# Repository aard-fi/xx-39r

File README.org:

* XX-39R                                                              :TOC_4:
- [[#overview][Overview]]
- [[#licensing][Licensing]]
- [[#quick-springtide-40-conversion-guide][Quick springtide 40 conversion guide]]
- [[#xx-39r265c27-3-the-original-hardware][XX-39R/265C27-3, the original hardware]]
- [[#elrs-replacement][ELRS replacement]]
  - [[#firmware][Firmware]]
    - [[#variants][Variants]]
    - [[#building][Building]]
    - [[#flashing][Flashing]]
    - [[#fuses][Fuses]]
  - [[#verify-functionality][Verify functionality]]

* Overview

This repository is for documenting a pretty bad receiver and motor driver board for a RC boat labeled =XX-39R= and =265C27-3=, as well as a replacement for it. The board can be found in models like "Revell Spring Tide 40", but has no place in a toy from this decade (or the last) - the reception is absolutely horrible, and there are better options available nowadays.

Read the sections below for a more detailed board description, as well as our "absolute overkill" option for replacing it with something better. While the replacement board is designed as drop in replacement for this model it has been designed with reusability for other small models in mind as well - which also would be listed here.

* Licensing

All source code is licensed under [[https://www.google.com/url?sa=t&source=web&rct=j&opi=89978449&url=https://www.gnu.org/licenses/old-licenses/gpl-2.0.en.html&ved=2ahUKEwir6f6Xoo6VAxVaGBAIHQJ2DeoQFnoECBIQAQ&usg=AOvVaw0XM7ZibsgscQZj5xHzFtb8][GPLv2]]. PCB related KiCad files are licensed under [[https://creativecommons.org/licenses/by-nc-sa/4.0/][CC BY-NC-SA 4.0]].

* Quick springtide 40 conversion guide

Open all the screws on the boat, and open the small electronics box. Submerge the board into isopropyl alcohol for roughly 24 hours - and while wet, remove the plugs. They should come out relatively easy now.
Remove the antenna wire from the hole, and remove the board.

Assuming you have a board populated with SMD components, now you'll need to

- solder JST-PH 2.0 headers into J1, J2, J3 and J4
- solder a jumper into or bridge J13
- solder a pin header (male or female - female might be more comfortabe with some programmers) into J5
- solder a pin header into J6. Recommendation would be angled male, and female on the ELRS receiver

The layout is the same as the original - the JST headers and the ELRS module most go to the underside of the board (inside the silk screen markings). For the programmer an angled header has space on top as well, and can allow for easier reflashing.

Next you can connect your UPDI programmer to the board and the PC, download the latest firmware archive from the release page, unzip, and run =flash.sh= (Linux/MacOS) or =flash.ps1= (Windows), and follow the instructions. Select the 10MHz springtide firmware, and decide if you want the water sensor.

Plug in the ELRS receiver and he motor, battery and sensor wires. Do a quick functionality test with batteries and a remote and then put everything together.

* XX-39R/265C27-3, the original hardware

The board is built around the [[https://www.talkingelectronics.com/projects/27MHz%20Transmitters/imagesP2/RX2Bdatasheet-5function.pdf][TX-2B/RX-2B]] transmitter/receiver combo. The problem here is less with that chip, but more that it can be used with the cheapest possible receiver circuit (in this case, tuned to 40MHz), which does not behave well in the real world.

The remote control has 4 buttons: binary inputs for reverse/forward for each of the motors. So no speed control, and steering by only using one motor (or reversing the other, for tight turns).

The motor controller is a [[https://www.lcsc.com/product-detail/Motor-Driver-ICs_Mixic-MX1616H_C5119044.html][MX1616H]] - which is a reasonable choice for a boat powered by 4.5V.

Additionally, there's a protection circuit to detect a current between the two motors to avoid activation outside of the water.

The schematic in the =pcb= directory currently should be mostly complete, with the exception of the receiver circuit.

* ELRS replacement

For our replacement we're relying on an ELRS receiver. While absolute overkill for such a boat it'll allow a nice upgrade path to larger models later on. The hardware can support any small receivers using a serial protocol - so if you have spare older receivers around it can be adapted to use that instead. We don't want to touch other parts of the boat - so while we could use 14500 cells instead of AA we'd have to lower the voltage to make sure we don't burn out the motors.

The easier way is to just stick with the 4.5V architecture, and only boost voltage for the ELRS receiver.

We can reuse the motor controller as well as the protection circuit - but as we want to support the cheapest possible ELRS remotes we can't rely on track mixing in the remote, and therefore need a cheap microcontroller to interface between the receiver and the motor controller. We can use an AtTiny414 for that - it'll work over the complete voltage range we can expect this to operate at. An AtTiny412 would be possible - but we'd have to reuse the UPDI pin.

All unused pins on the MCU are lead out, as well as some spare footprints for VCC and GND pins. The complete table of pin headers is:

| Reference | Description     | Comment                                                                |
|-----------+-----------------+------------------------------------------------------------------------|
| J1        | Sense           |                                                                        |
| J2        | Battery         | Designed for 4.5V, but can take up to 5.5V                             |
| J3        | Port motor      |                                                                        |
| J4        | Starboard motor |                                                                        |
| J5        | UPDI            |                                                                        |
| J6        | Receiver        | Designed for ELRS, but can be used otherwise as well. See pinout below |
| J7        | PA6             |                                                                        |
| J8        | PA1             |                                                                        |
| J9        | PA3             |                                                                        |
| J10       | PA2             |                                                                        |
| J11       | Spare VCC       |                                                                        |
| J12       | Spare VCC       |                                                                        |
| J13       | Receiver VCC    | Bridge to use the on board booster, or connect your own                |
| J14       | Spare GND       |                                                                        |
| J15       | Spare GND       |                                                                        |
| J16       | Spare GND       |                                                                        |

The header for the (ELRS) receiver (=J6=) has the following pinout:

| Pin | ELRS | MCU           | Pin |
|-----+------+---------------+-----|
|   1 | GND  | GND           |     |
|   2 | VCC  | -             |     |
|   3 | TX   | PB3, UART1 RX |   6 |
|   4 | RX   | PB2, UART1 TX |   7 |

Any receiver using a serial protocol (like FlySky AFHDS) could be used, though the firmware here only supports ELRS.

The motor headers are connected as follows:

|           |          |       |      |     |          |
|-----------+----------+-------+------+-----+----------|
| Port      | J3 pin 1 | OUTA1 | INA1 | PA4 | =M1_FWD=   |
|           | J3 pin 2 | OUTB1 | INB1 | PA5 | =M1_REV=   |
| Starboard | J4 pin 1 | OUTA2 | INA2 | PB0 | =M2_FWD=   |
|           | J4 pin 2 | OUTB2 | INB2 | PB1 | =M2_REV= |

** Firmware

This is build with =common.hpp= containing code for all bigger features, and the individual firmware variants can use that to build model specific variants in less than 50 lines of code.

Common features are

- direction-change dead time (~50–80 ms coast) prevents regenerative voltage spikes
- rate limiting (±25 PWM per packet accel) makes it both more controllable (kid friendly) and prevents hardware destroying voltage spikes
- low-voltage cutoff (2.8 V) can stop motors before brownout
- custom CRSF parser, somewhat resilient: we try to re-sync if we read too much garbage, and stop the motors if we can't get it back
- water sensor readings, in safety mode (motors directly shut off) or just reading for extra data
- battery voltage readings
- support for different CPU speeds: 5, 10, 16 and 20MHz
- simple RX and TX buffering for UART communications
- optional "kickstart" support: on slow speeds do occasional kicks to get the motor started

*** Variants

We can build variants with extra features from base sources, with the filename containing markers to show what it is:

- *-ks* — Motor kickstart enabled (helps low-speed startup)
- *-ws* — Water safety sensor enabled. Recommended for kids - motors stop when the boat is removed from the water.
- *-5m*, *-10m*, *-16m* — CPU frequency variants (default = 20 MHz)

All release builds have frequency markers, only manual builds for development targets come without that, in which case 20MHz is assumed.

When running a model from batteries you generally should be using the 10MHz variant - that should be stable until relatively low voltages still. See fuse settings below if you want to push it even further by utilising brownout detection.

*** Building

Building only requires [[https://gcc.gnu.org/wiki/avr-gcc][avr-gcc]], and avr-libc in a variant new enough to have headers compatible with AtTiny414. On any sensible Linux distribution just installing those via the package manager should be fine, if you're using Ubuntu you can get a recent enough binary tarball via [[https://github.com/modm-io/avr-gcc][modm-io]].

On MacOS via homebrew you could do =brew tap osx-cross/avr && brew install avr-gcc@15=. Make sure it's in your path - either add it, or force linking it.

=make all-freqs= builds all variants.  Individual targets work too:

=make build/firmware-test-10m.hex= builds a single suffixed hex for 10 MHz.

=make FREQ=10m MOTOR_STALL_SPEED=120 all= customises stall speed before building.

*** Flashing

Flashing requires avrdude, as well as some UPDI programmer. Something like the [[https://www.adafruit.com/product/5879][UPDI friend]] is recommended, though you can [[https://github.com/ElTangas/jtag2updi][use some old Arduino]] as well.

When building from source =make flash= can be used - it will try to write =firmware.hex= to a UPDI programmer at =/dev/ttyUSB1=. You can override the firmware to flash with the =TARGET= variable, and the serial port with =PORT=: =make flash TARGET=firmware-test-pwm-starboard TARGET=/dev/ttyUSB0= would write the starboard motor test firmware via =ttyUSB0=.

Directly with avrdude the command for that would be =avrdude -c serialupdi -p t414 -U flash:w:firmware-test-pwm-starboard.hex:i -P /dev/ttyUSB0=

If you downloaded a release with prebuilt hex files, use the interactive scripts in =scripts/=:

- macOS / Linux: =./scripts/flash.sh=
- Windows: =powershell -ExecutionPolicy Bypass -File .\scripts\flash.ps1=

These scripts auto-detect your programmer, show current fuse values in plain English, and guide you through firmware selection.

*** Fuses

There are two fuses interesting for us:

- *BODCFG = 0x0A* — Brown-out detection enabled at 2.6 V
- *OSCCFG = 0x02* — 20 MHz internal oscillator

OSCCFG only needs to be set when running at 16MHz.

BODCFG configures the brownout detector, which can be useful to ensure the system gets back into a defined state when playing close to voltage limits.

Set with avrdude, or the included flash scripts.

** Verify functionality

This repository contains various specialised firmware bits to help debugging.

If the serial port is not working:

- flash =firmware-test-pb2= and check for a square wave on the =TX= pin of the ELRS header, and move on to =PB2= (pin 7) if there is none. This will either verify that the pin can be used - or point towards a hardware issue
- if the square wave test worked flash =firmware-test-uart= - this should be visible on the oscilloscope with the same settings, and a connected serial adapter should start printing =U=

For testing the motors:

- flash =firmware-test-gpio=. This will print to the serial port what it is testing, and will bitbang each motor port. Connected motors should spin up (in both directions), and this should be visible on a multimeter or oscilloscope
- flash =firmware-test-port= or =firmware-test-starboard= - those will cycle the port/starboard motor through reverse and forward PWM. If both spin correctly in both directions the motors are fine

For testing the water sensing:

- flash =firmware-test-water= and bridge J1, either with finger/metal or by sticking cables into water. It'll dump readings via serial

With all of the above sorted out you can flash =firmware-test= for a simple interactive serial interface to control all of the above. It'll spam a banner to serial until it receives a first keypress.

Steering should be channel 1 idle 0, -100 to 100. throttle should be channel 3, idle -100, up to 100.

Channels 5 and 8 may be used as toggle switches, channels 6 and 7 as tristate switches.

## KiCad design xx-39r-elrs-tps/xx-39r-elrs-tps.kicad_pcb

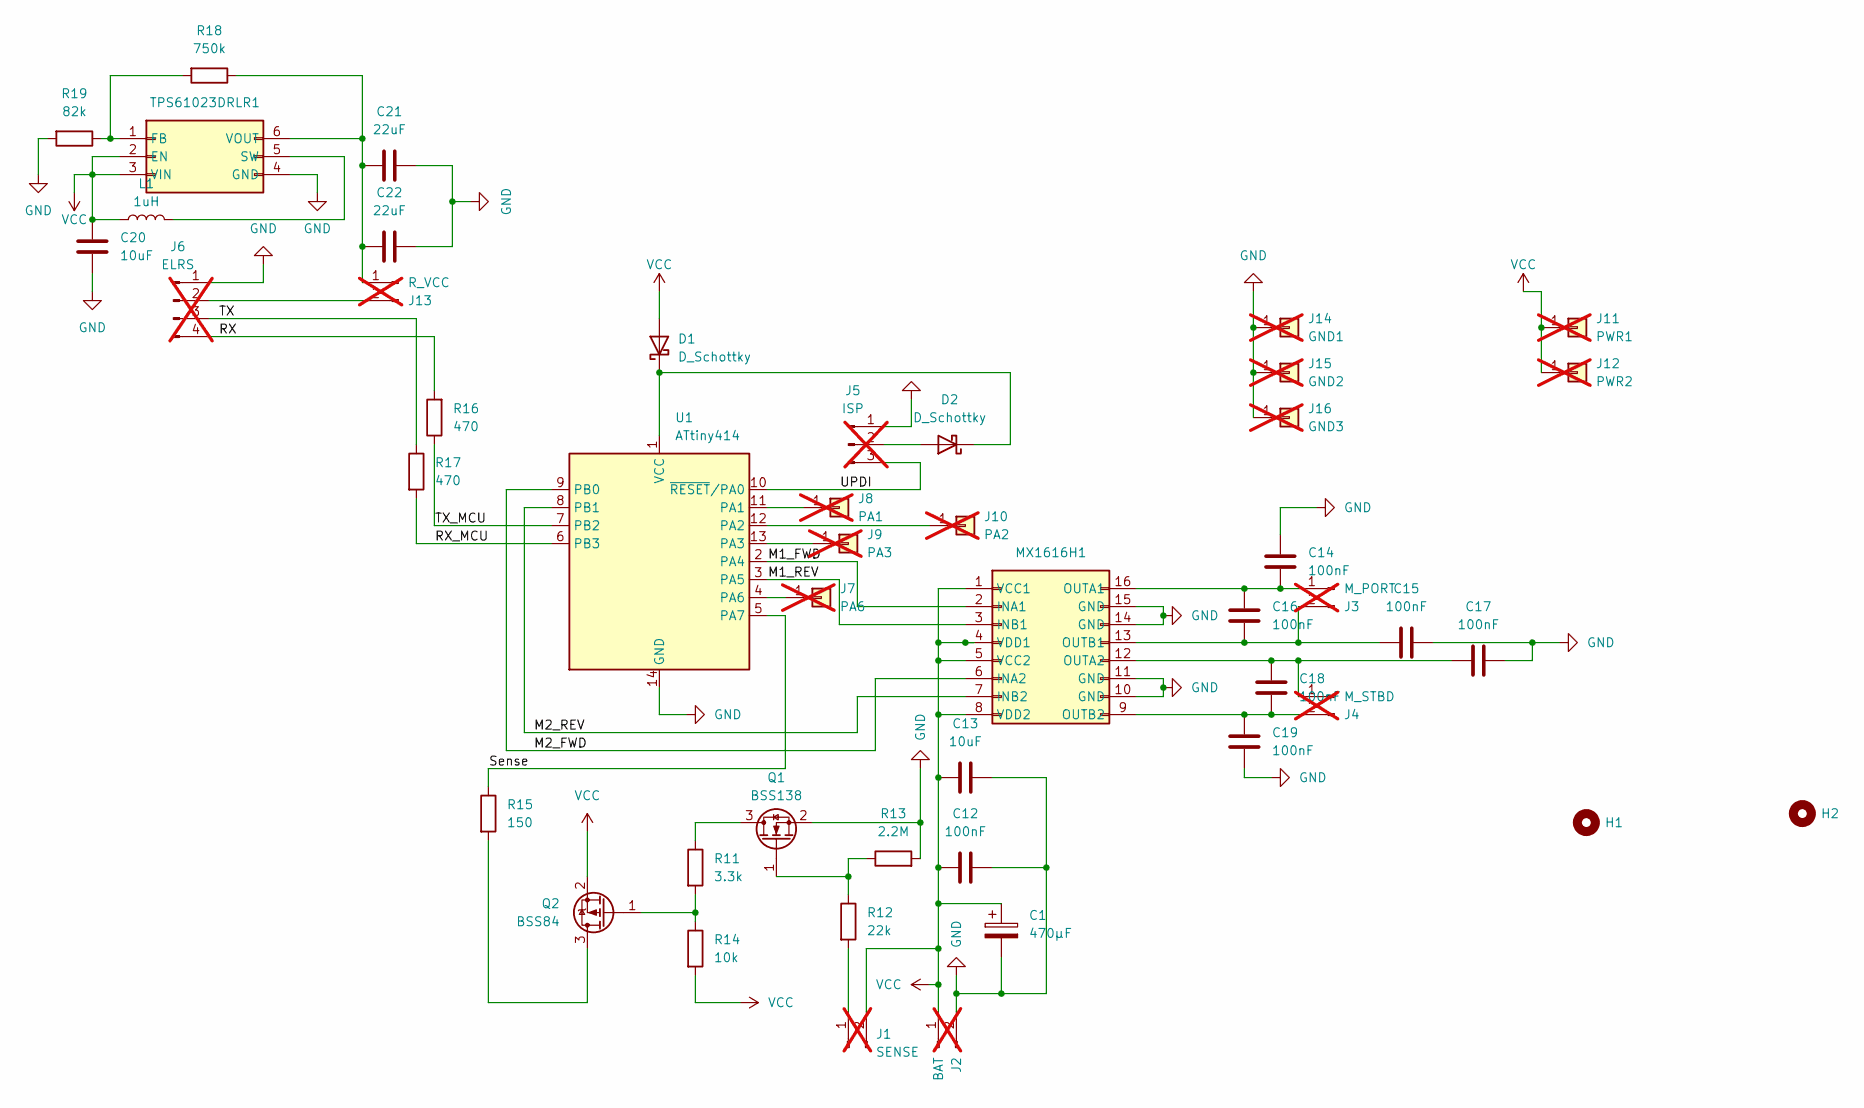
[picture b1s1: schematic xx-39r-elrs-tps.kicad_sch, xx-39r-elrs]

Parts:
C1: 470µF; CP_Elec_6.3x5.4; LCSC C7469933
C12, C14, C15, C16, C17, C18, C19: 100nF; C_0402_1005Metric
C13, C20: 10uF; C_0603_1608Metric
C21, C22: 22uF; C_0805_2012Metric
D1, D2: D_Schottky; D_SOD-123; LCSC C7370889
H1, H2: MountingHole_3mm
J1: SENSE; JST_PH_S2B-PH-K_1x02_P2.00mm_Horizontal; not fitted
J2: BAT; JST_PH_S2B-PH-K_1x02_P2.00mm_Horizontal; not fitted
J3: M_PORT; JST_PH_S2B-PH-K_1x02_P2.00mm_Horizontal; not fitted
J4: M_STBD; JST_PH_S2B-PH-K_1x02_P2.00mm_Horizontal; not fitted
J5: ISP; PinHeader_1x03_P2.54mm_Vertical; not fitted
J6: ELRS; PinHeader_1x04_P2.54mm_Vertical; not fitted
J7: PA6; PinHeader_1x01_P2.54mm_Vertical; not fitted
J8: PA1; PinHeader_1x01_P2.54mm_Vertical; not fitted
J9: PA3; PinHeader_1x01_P2.54mm_Vertical; not fitted
J10: PA2; PinHeader_1x01_P2.54mm_Vertical; not fitted
J11: PWR1; PinHeader_1x01_P2.54mm_Vertical; not fitted
J12: PWR2; PinHeader_1x01_P2.54mm_Vertical; not fitted
J13: R_VCC; PinHeader_1x02_P2.54mm_Vertical; not fitted
J14: GND1; PinHeader_1x01_P2.54mm_Vertical; not fitted
J15: GND2; PinHeader_1x01_P2.54mm_Vertical; not fitted
J16: GND3; PinHeader_1x01_P2.54mm_Vertical; not fitted
L1: 1uH; L_1008_2520Metric; LCSC C286537
MX1616H1: SOIC-16_3.9x9.9mm_P1.27mm; LCSC C5119044
Q1: BSS138; SOT-23; LCSC C7420339
Q2: BSS84; SOT-23; LCSC C114481
R11: 3.3k; R_0603_1608Metric
R12: 22k; R_0603_1608Metric
R13: 2.2M; R_0603_1608Metric
R14: 10k; R_0603_1608Metric
R15: 150; R_0603_1608Metric
R16, R17: 470; R_0603_1608Metric
R18: 750k; R_0603_1608Metric
R19: 82k; R_0603_1608Metric
TPS61023DRLR1: SOT-563; LCSC C919459
U1: ATtiny414; SOIC-14_3.9x8.7mm_P1.27mm; LCSC C189365

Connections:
/M1_FWD: MX1616H1.2 (INA1), U1.2 (PA4)
/M1_REV: MX1616H1.3 (INB1), U1.3 (PA5)
/M2_FWD: MX1616H1.6 (INA2), U1.9 (PB0)
/M2_REV: MX1616H1.7 (INB2), U1.8 (PB1)
/RX: J6.4, R16.2
/RX_MCU: R17.2, U1.6 (PB3)
/Sense: R15.1, U1.5 (PA7)
/TX: J6.3, R17.1
/TX_MCU: R16.1, U1.7 (PB2)
/UPDI: J5.3, U1.10 (~RESET/PA0)
GND: C1.2, C12.2, C13.2, C14.1, C15.2, C17.2, C19.2, C20.1, C21.1, C22.1, J2.2, J5.1, J6.1, J14.1 (Pin_1_1), J15.1 (Pin_1_1), J16.1 (Pin_1_1), MX1616H1.10 (GND), MX1616H1.11 (GND), MX1616H1.14 (GND), MX1616H1.15 (GND), Q1.2 (S), R13.2, R19.2, TPS61023DRLR1.4 (GND), U1.14 (GND)
unnamed: D1.1 (K), D2.1 (K), U1.1 (VCC)
unnamed: D2.2 (A), J5.2
unnamed: J1.1, R12.2
unnamed: C14.2, C16.1, J3.1, MX1616H1.16 (OUTA1)
unnamed: C15.1, C16.2, J3.2, MX1616H1.13 (OUTB1)
unnamed: C17.1, C18.1, J4.1, MX1616H1.12 (OUTA2)
unnamed: C18.2, C19.1, J4.2, MX1616H1.9 (OUTB2)
unnamed: J7.1 (Pin_1_1), U1.4 (PA6)
unnamed: J8.1 (Pin_1_1), U1.11 (PA1)
unnamed: J9.1 (Pin_1_1), U1.13 (PA3)
unnamed: J10.1 (Pin_1_1), U1.12 (PA2)
unnamed: C21.2, C22.2, J13.1, R18.1, TPS61023DRLR1.6 (VOUT)
unnamed: J6.2, J13.2
unnamed: Q1.3 (D), R11.1
unnamed: Q1.1 (G), R12.1, R13.1
unnamed: Q2.3 (D), R15.2
unnamed: Q2.1 (G), R11.2, R14.1
unnamed: R18.2, R19.1, TPS61023DRLR1.1 (FB)
unnamed: L1.2, TPS61023DRLR1.5 (SW)
VCC: C1.1, C12.1, C13.1, C20.2, D1.2 (A), J1.2, J2.1, J11.1 (Pin_1_1), J12.1 (Pin_1_1), L1.1, MX1616H1.1 (VCC1), MX1616H1.4 (VDD1), MX1616H1.5 (VCC2), MX1616H1.8 (VDD2), Q2.2 (S), R14.2, TPS61023DRLR1.2 (EN), TPS61023DRLR1.3 (VIN)

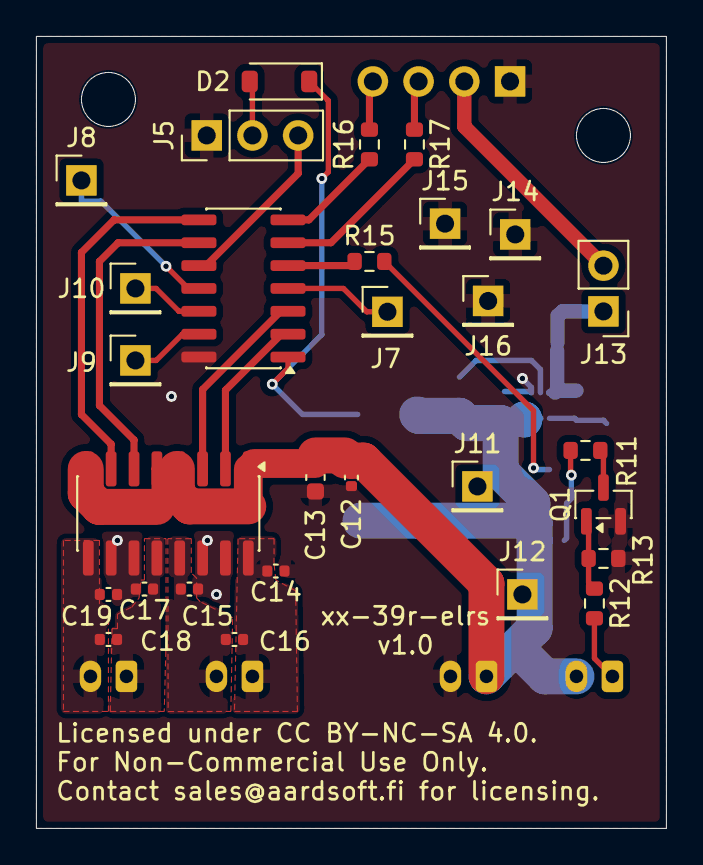
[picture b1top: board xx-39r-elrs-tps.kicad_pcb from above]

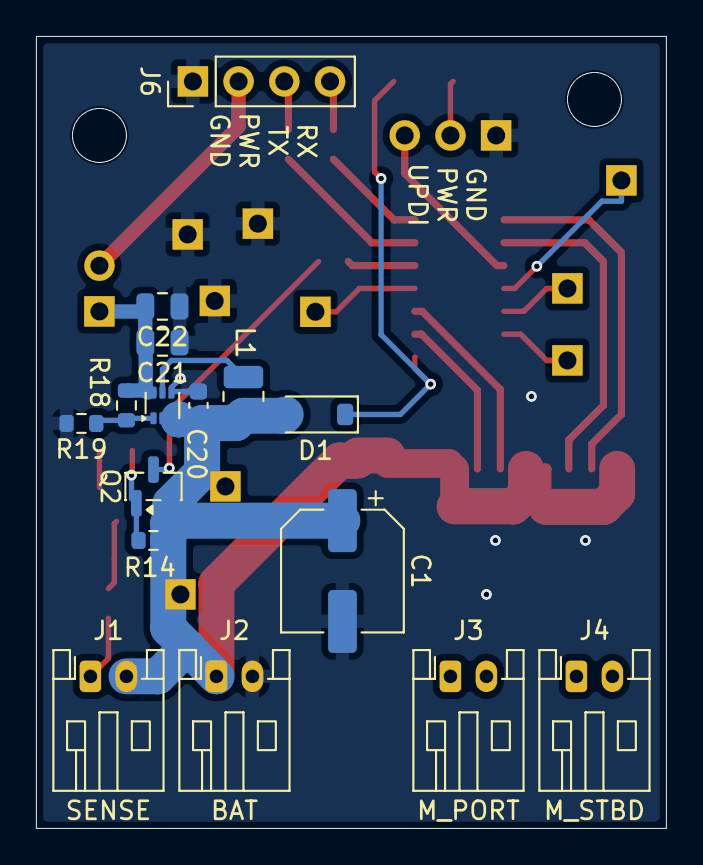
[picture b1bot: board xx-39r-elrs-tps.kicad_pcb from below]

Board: 2 copper layers, 35.0 x 44.0 mm, 47 parts (16 on the bottom side), 31 nets.

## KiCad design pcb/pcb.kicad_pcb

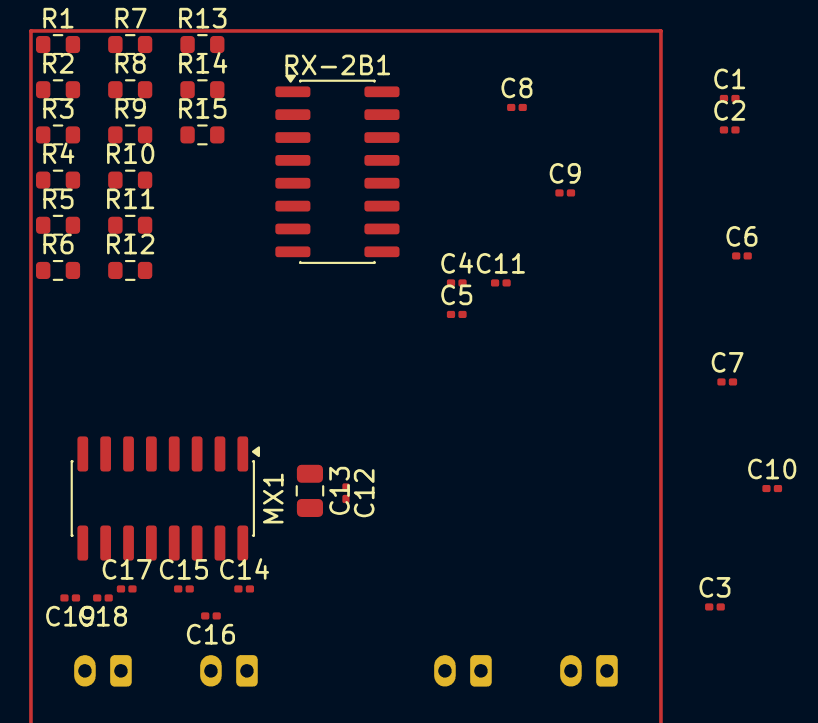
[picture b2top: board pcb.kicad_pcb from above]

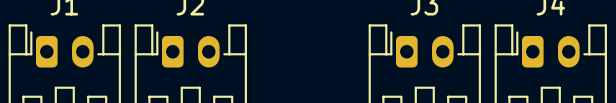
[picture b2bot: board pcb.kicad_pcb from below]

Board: 2 copper layers, 40 parts (4 on the bottom side), 10 nets, no tracks yet.

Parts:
C1, C2, C3, C4, C5, C6, C7, C8, C9, C10, C11, C12, C14, C15, C16, C17, C18, C19: 100nF; C_0201_0603Metric
C13: 10uF; C_0805_2012Metric
J1: SENSE; JST_PH_S2B-PH-K_1x02_P2.00mm_Horizontal
J2: BAT; JST_PH_S2B-PH-K_1x02_P2.00mm_Horizontal
J3: M_PORT; JST_PH_S2B-PH-K_1x02_P2.00mm_Horizontal
J4: M_STBD; JST_PH_S2B-PH-K_1x02_P2.00mm_Horizontal
MX1: SOIC-16_3.9x9.9mm_P1.27mm
R1, R2, R3, R4, R5, R6, R7, R8, R9, R10, R11, R12, R13, R14, R15: R; R_0603_1608Metric
RX-2B1: SOIC-16_3.9x9.9mm_P1.27mm

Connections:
GND: C12.2, C13.2, C14.1, C15.2, C17.2, C19.2, J2.2, MX1.10 (GND), MX1.11 (GND), MX1.14 (GND), MX1.15 (GND)
unnamed: C12.1, C13.1, J2.1, MX1.1 (VCC1), MX1.4 (VDD1), MX1.5 (VCC2), MX1.8 (VDD2)
unnamed: C14.2, C16.1, J3.1, MX1.16 (OUTA1)
unnamed: C15.1, C16.2, J3.2, MX1.13 (OUTB1)
unnamed: C17.1, C18.1, J4.1, MX1.12 (OUTA2)
unnamed: C18.2, C19.1, J4.2, MX1.9 (OUTB2)
unnamed: MX1.2 (INA1), RX-2B1.11 (FORWARD)
unnamed: MX1.6 (INA2), RX-2B1.7 (LEFT)
unnamed: MX1.3 (INB1), RX-2B1.10 (BACKWARD)
unnamed: MX1.7 (INB2), RX-2B1.6 (RIGHT)

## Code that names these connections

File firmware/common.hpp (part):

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 *          [STERN]
 *
 * Board wiring:
 *   PA4 -> INA1 (Port motor forward PWM  -> TCA0 HCMP1 / WO4)
 *   PA5 -> INB1 (Port motor backward PWM -> TCA0 HCMP2 / WO5)
 *   PB0 -> INA2 (Starboard motor forward PWM -> TCA0 LCMP0 / WO0)
 *   PB1 -> INB2 (Starboard motor backward PWM-> TCA0 LCMP1 / WO1)
 *   PA7 -> Water detection sense input (with pull-up)
 *   PB2 -> Receiver RX
 *   PB3 -> Receiver TX
 */

#ifndef COMMON_HPP
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
static inline void initPins() {
  // motor driver outputs (TCA0 will override when enabled)
  PORTA.DIRSET = PIN4_bm | PIN5_bm;   // PA4=INA1, PA5=INB1
  PORTB.DIRSET = PIN0_bm | PIN1_bm;   // PB0=INA2, PB1=INB2

  // UART debug on PB2/PB3 (default USART0 pins on ATtiny414)
  PORTB.DIRSET = PIN2_bm;             // PB2 = TXD
  PORTB.DIRCLR = PIN3_bm;             // PB3 = RXD

  // water detection sense input - no pullup, and we set up ADC later so
  // we can easily define thresholds what we count as "water detected"
  PORTA.DIRCLR = WATER_SENSE_bm;
}

// UART setup (PB2/PB3, 115200 baud — BAUD value derived from F_CPU)
static inline void initUART() {
  USART0.BAUD = USART_BAUD;
  USART0.CTRLB = USART_RXEN_bm | USART_TXEN_bm;
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// PWM helpers
//
// initialise TCA0 in split mode and enable waveform output on all channels.
// PA4/PA5 and PB0/PB1 are the default pins for WO4/WO5 and WO0/WO1,
// so no PORTMUX is required. If you need a PWM channel not going via the motor
// controller your only option would be WO3 on PA3 (J9), also default pin. If
// you need more you'll either have to bitbang, or remap serial: WO2 is on PB2,
// WO3 can be remapped to PB3. The alt serial pins PA1/PA2 are available on
// J8 and J10.
//
// if a caller needs only one motor, just set the other to 0 via setMotorXxx(0).
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  TCA0.SPLIT.CTRLA = 0;

  // TCA0 split mode:
  // L-counter: LCMP0->PB0 (INA2, stbd forward)
  //            LCMP1->PB1 (INB2, stbd backward)
  // H-counter: HCMP1->PA4 (INA1, port forward)
  //            HCMP2->PA5 (INB1, port backward)
  TCA0.SPLIT.CTRLD = TCA_SPLIT_SPLITM_bm;
  // with my test motors DIV1 starts motors at roughly 140 PWM signal, DIV4
  // at 150 and DIV16 at 160 - so seems it makes sense to stick with a
  // relatively high PWM frequency here
  TCA0.SPLIT.CTRLA = TCA_SPLIT_CLKSEL_DIV1_gc | TCA_SPLIT_ENABLE_bm;
  TCA0.SPLIT.CTRLB = TCA_SPLIT_LCMP0EN_bm      // PB0 = stbd forward
    | TCA_SPLIT_LCMP1EN_bm    // PB1 = stbd backward
    | TCA_SPLIT_HCMP1EN_bm    // PA4 = port forward
    | TCA_SPLIT_HCMP2EN_bm;   // PA5 = port backward
  TCA0.SPLIT.LPER = PWM_MAX;
  TCA0.SPLIT.HPER = PWM_MAX;
  TCA0.SPLIT.LCMP0 = 0;
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
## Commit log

2026-06-03 Import initial stage of reverse engineering of XX-39R board
    Mainly the antenna section is missing now
2026-06-17 Add firmware, documentation and test bits
2026-06-17 Add GPLv2 license
2026-06-17 Add v1 pcb and related license information
2026-06-17 Add delay for ADC readings
    Original code worked by accident, presumably due to shared ground on
    the bench PSU. With a more isolated PSU things went wrong, until the
    delay got added. I really should start remembering that, can't recount
    how often I ran into that with Atmel CPUs.
2026-06-17 Add comment about PWM frequency tests
2026-06-17 Add experimental support for kicking the motor on low speeds
    We'll eventually need to map out the range where the motors definitely
    don't work - but by kicking the min we might be able to increase the
    range a bit. This is intentionally a separate compile flag, and
    produces separate firmware files, as it may not end up being a good thing.
2026-06-22 Use 0805 for C21/C22
    The actual capacitance of the old 0402 might drop below TPS
    requirements under load.
2026-06-25 Add a separate copy of the board with integrated boost converter
    Tests have shown modern ELRS receivers _may_ be fine running directly
    off 3 AA cells, even with some voltage sagging, so we'll explore that
    in the default layout, and keep this for the integrated voltage
    booster.
    Moving the voltage booster off the default, and just providing a 3-pin
    header for plugging in an optional booster PCB has a few advantages:
2026-06-25 Change R19 to 100K
    With the 82K we were ending up with 5.8V boosted output, which made
    the TPS cook itself. This now lowers it to a safe 5.2V with what I
    have at hand (should be closer to 5V).
2026-06-25 Add separate springtide40 firmware
    Target is firmware optimised for this specific hardware, while we can
    do a bit more experiments in the main firmware.
2026-06-27 Add 5/10/16MHz variants
    At 20MHz we'd need a stable 4.5V supply - which we can't guarantee on
    3 AA cells, and definitely won't have with nimh or 1S lipos. Best
    compromise is probably 10MHz (stable down to 2.7V), but to make it
    easy to switch this removes clock specific codes, and adds support for
    building the firmware in variants for 5/10/16 and 20MHz. 16MHz
    requires changing the fuse for selecting the oscillator.
2026-06-27 Prepare custom PWM frequencies
    Motors seem to behave better at low speed at high frequencies, but
    lowering the clock reduces the default frequencies -> we raise them
    again, at the cost of resolution.
    This alters the maximum value we should be writing to PWM registers -
    so this commit alone introduces unwanted behaviour, as we're still
    using 255 everywhere. An upcoming commit will fix that by introducing
2026-06-28 github: build all firmware variants
2026-06-28 Add proper logic for CRSF, water sensor and battery reading
    - add a custom minimalistic CRSF implementation, copying all channels
    we might care about into a global struct
    - add timer driven water sensor and battery reading - with water
    sensor readings frequent enough that it can be used as safety device
    - implement protection functions in the main motor wrappers to prevent
    fast direction/speed changes. In extreme situations we may be able
2026-06-28 Create release archives with flasher scripts
    The Windows variant is fully untested so far.
2026-06-28 Add the new water safety stuff to the main firmware
2026-06-28 Use shared (and improved) CRSF code for springtide model
2026-06-29 Update documentation

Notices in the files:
firmware/common.hpp:
@copyright Copyright (c) 2026 Bernd Wachter
xx-39r-elrs-tps/xx-39r-elrs-tps.kicad_pcb:
Licensed under CC BY-NC-SA 4.0.
xx-39r-elrs-tps/xx-39r-elrs-tps.kicad_sch:
Licensed under CC BY-NC-SA 4.0. For Non-Commercial Use Only.
